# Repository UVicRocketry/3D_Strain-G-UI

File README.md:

# 3D_Strain-G-UI
Welcome to 3D_Strain-G-UI: a 3D PyQT/PyQTGraph GUI for rocket fuselage bending analysis using strain gauges!

Originally designed for Uvic Rocketry's 10k/Xenia-1 rocket, it is a general piece of software capable of supporting any number of strain gauges, and any rocket shape.

## Basic Requirements
* python3 and pip3
* The following libraries installed using pip3
	* PyQT5
	* numpy
	* numpy-stl
	* pyserial
	* pyqtgraph
	* pyopengl
	* qdarkstyle

Additionally, if you would like to use the live mode of this software, an Arduino programmed with `MPU6050_Demp_Sketch.ino` or similar device capable of serial communication should be connected to the computer.

## Setup
First clone the respository
```
git clone https://github.com/UVicRocketry/3D_Strain-G-UI
```
Then open a terminal in the `3D_Strain-G-UI` folder and run
```
python 3D_Backend.py
```
to start the program.

## Interface Overview
Upon first launch, the following interface is shown. This shows graphs of stats such as yaw, pitch, roll, altitude, etc.

_Note: only some of these graphs are implemented right now_

Selecting Tab2 of the UI, the main interface is shown.

Here is where the magic happens. The upper left of the UI contains file management controls, below are playback controls, and bottom left are current rocket environmental variables.

## Selecting a Rocket
3D-Strain-G-UI allows `.rocket` configuration files to be loaded via the `Load Rocket` button. A sample rocket called `10K.rocket` is included for testing.

## Loading a Log File
CSV log files formatted as `time,yaw,pitch,roll,altitude,strain1,strain2....` can be loaded for playback using the `Load Log File` button. A sample log file called `Sample_Flight_Data.csv` is included for testing with `10K.rocket`.

## Basic Usage
Load the `10K.rocket` and `Sample_Flight_Data.csv` files into the program. This should show a model of SpaceX's starship created by Arturo R. 

Next, test the playback by pressing play button. The Starship should display strain data, altitude, etc as it reads the log file.

Click and drag on the rocket to orbit around. Zoom using the scroll wheel, and pan using scroll click. Pause playback using the play button, and reset to the initial view using the `Reset View` button.

Using the slider under the 3D view, scrub through the log file to find apogee. Adjust the framerate slider and begin playback to watch the apogee in slow motion.

Pause playback during a particularly colorful section of the logfile which indicates high strain. In the table beneath the Yaw, Pitch etc. data, select a cell to highlight the strain sensor on the rocket responsible for that data. The section of the model will glow pink when selected.

## Creating a Model
Since the models used by the software are `.STL`, any CAD program can be used to create them. 

Specific naming must be used for the strain sections of the following form: `foo-strain_section-n.STL` where n = 1,2,3,4... It is recommended to use linear and radial patterns to automatically number the parts according to this naming convention, however the parts can be named manually as well. Arturo's Starship Solidworks assembly is included as a reference. Other components of the assembly do not need to follow any particular naming convention. Shown below is the feature tree of the included assembly.

To ensure that the rocket in the 3D view orbits around the center of mass, the assembly must be treated in a certain way. First, mate the CoM of the assembly to the origin of the assembly. Then, when exporting the assembly as an STL, click options, then check the box labled "Do not translate STL output data to positive space".

## Creating a .Rocket Configuration
Configuration files can be created that specify the location of STL files, color sensitivity and other parameters. Below is the `10K.rocket` config included.

```
{
    "NAME": "Arturo's Starship",
    "STL_DIRECTORY" : "STL_Files",
    "RINGS" : 3,
    "SG_PER_RING" : 4,
    "COLOR_SENSITIVITY" : 0.02
}
```

This file can be reused as is with the `STL_DIRECTORY` changed to the relative location of the STLs desired. `RINGS` and `SG_PER_RING` are discussed in the next section.

## Ring Terminology
The software was originally written to consider the strain gauges in "rings" that are placed circumferentially at a given section of the fuselage. Multiple rings are placed at various points of the fuselage to measure strain in those areas. Later however, it was determined that this is not a limitation that need to be applied to the software, and strain gauges do not need to be organized in the fashion. The code could be easily adapted to support say strain gauges in the fins or nosecone. Regardless, the terminology stuck, so until the code is modified, this is how things are.

What this means is in configuration files, the number of rings, and number of strain gauges per ring must be specified. The included sample files contain 12 strain gauges arranged in 3 rings of 4 gauges. The `.rocket` file reflects this.

## Further Work
It would be nice to implement the rest of the graphs in Tab1. Also, removing any ring structure dependence in the code would help to simplify the code and make it more flexible. The `Rocket` class should also be split into a seperate file to make the source files smaller.

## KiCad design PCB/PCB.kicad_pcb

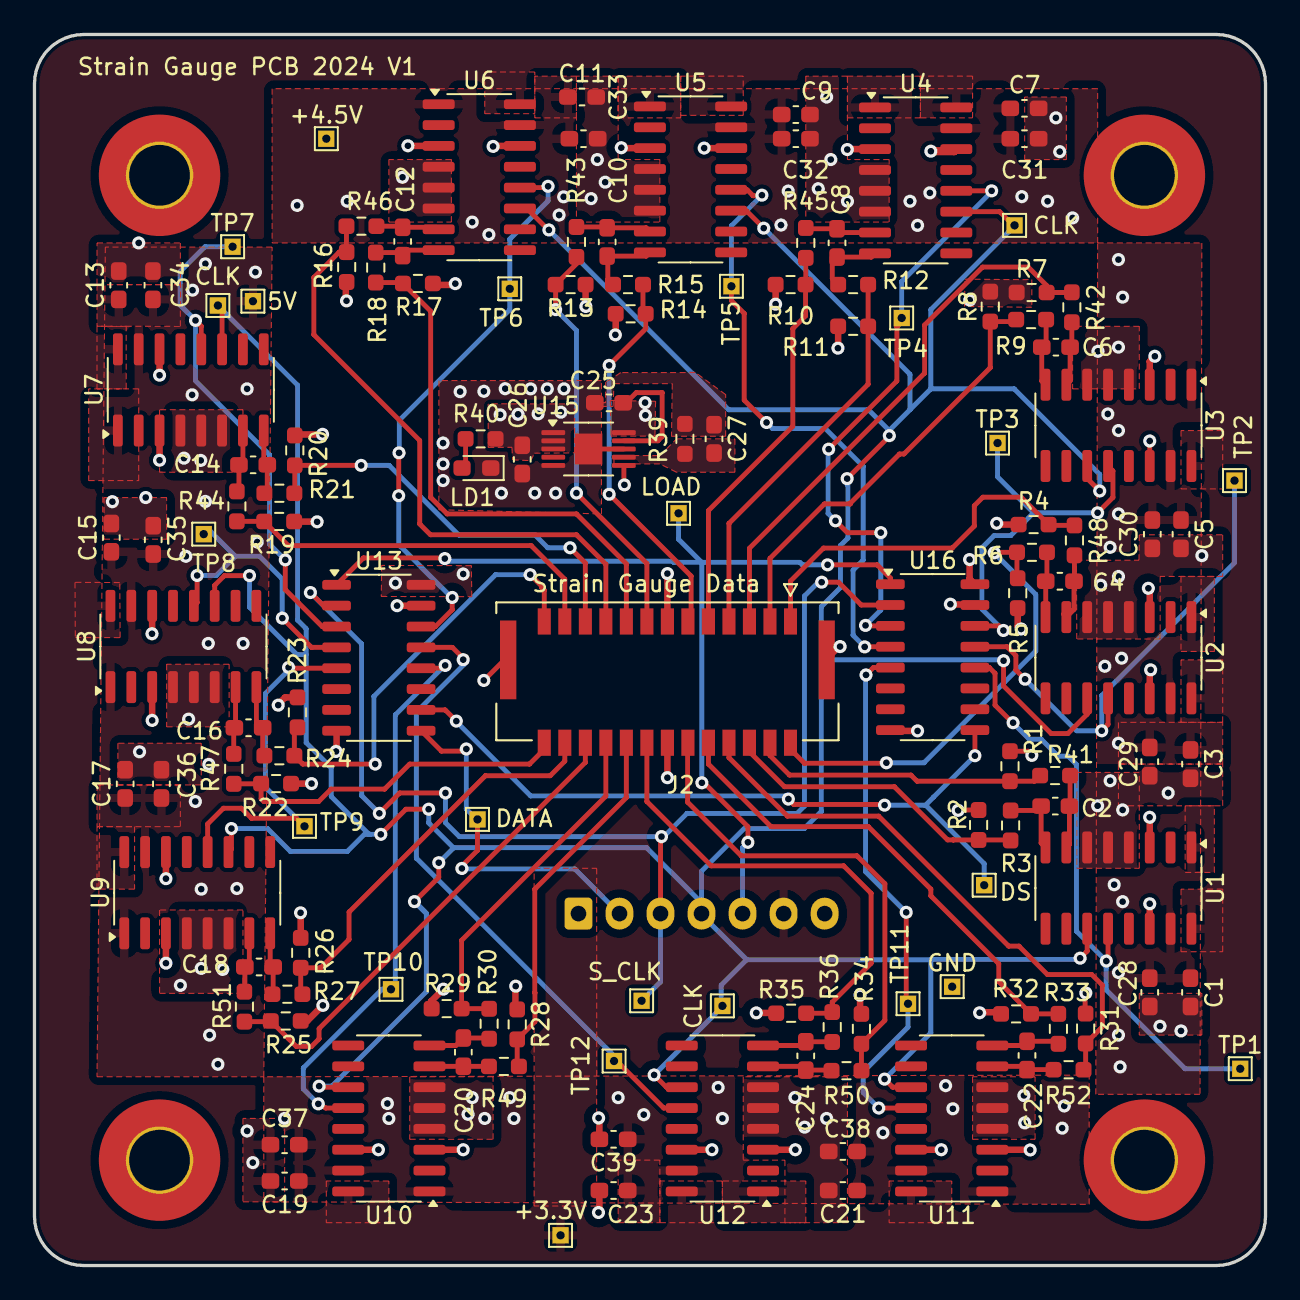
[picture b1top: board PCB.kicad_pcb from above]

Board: 4 copper layers, 75.0 x 75.0 mm, 134 parts (1 on the bottom side), 71 nets.

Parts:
5V: 5V; TestPoint_THTPad_1.0x1.0mm_Drill0.5mm
+3.3V: 3.3V; TestPoint_THTPad_1.0x1.0mm_Drill0.5mm
+4.5V: 4.5V; TestPoint_THTPad_1.0x1.0mm_Drill0.5mm
C1, C3, C5, C7, C9, C11, C13, C15, C17, C19, C21, C23: 10U; C_0603_1608Metric_Pad1.08x0.95mm_HandSolder
C2, C4, C6, C8, C10, C12, C14, C16, C18, C20, C22, C24, C28, C29, C30, C31, C32, C33, C34, C35, C36, C37, C38, C39: U01; C_0603_1608Metric_Pad1.08x0.95mm_HandSolder
C25, C26, C27: 4.7U; C_0603_1608Metric_Pad1.08x0.95mm_HandSolder
CLK: HX_CLK; TestPoint_THTPad_1.0x1.0mm_Drill0.5mm
CLK#2, CLK#3: HX_CLK; TestPoint_THTPad_1.0x1.0mm_Drill0.5mm
DATA: DATA; TestPoint_THTPad_1.0x1.0mm_Drill0.5mm
DS: DS; TestPoint_THTPad_1.0x1.0mm_Drill0.5mm
GND: GND; TestPoint_THTPad_1.0x1.0mm_Drill0.5mm
H1, H2, H3, H4: MountingHole; MountingHole_3.7mm_Pad_TopBottom
J1: Conn_01x06_Female; JST_XH_B7B-XH-A_1x07_P2.50mm_Vertical
J2: 5054332681; MOLEX_5054332681
LD1: LED; LED_0603_1608Metric_Pad1.05x0.95mm_HandSolder
LOAD: LOAD; TestPoint_THTPad_1.0x1.0mm_Drill0.5mm
R1, R2, R4, R5, R7, R8, R10, R11, R13, R14, R16, R17, R19, R20, R22, R23, R25, R26, R28, R29, R31, R32, R34, R35: 350; R_0603_1608Metric_Pad0.98x0.95mm_HandSolder
R3, R6, R9, R12, R15, R18, R21, R24, R27, R30, R33, R36, R41, R42, R43, R44, R45, R46, R47, R48, R49, R50, R51, R52: 100; R_0603_1608Metric_Pad0.98x0.95mm_HandSolder
R39: 45K; R_0603_1608Metric_Pad0.98x0.95mm_HandSolder
R40: 1k; R_0603_1608Metric_Pad0.98x0.95mm_HandSolder
S_CLK: S_CLK; TestPoint_THTPad_1.0x1.0mm_Drill0.5mm
TP1: SG1; TestPoint_THTPad_1.0x1.0mm_Drill0.5mm
TP2: SG2; TestPoint_THTPad_1.0x1.0mm_Drill0.5mm
TP3: SGD3; TestPoint_THTPad_1.0x1.0mm_Drill0.5mm
TP4: SG4; TestPoint_THTPad_1.0x1.0mm_Drill0.5mm
TP5: SG5; TestPoint_THTPad_1.0x1.0mm_Drill0.5mm
TP6: SG6; TestPoint_THTPad_1.0x1.0mm_Drill0.5mm
TP7: SG7; TestPoint_THTPad_1.0x1.0mm_Drill0.5mm
TP8: SG8; TestPoint_THTPad_1.0x1.0mm_Drill0.5mm
TP9: SG9; TestPoint_THTPad_1.0x1.0mm_Drill0.5mm
TP10: SG10; TestPoint_THTPad_1.0x1.0mm_Drill0.5mm
TP11: SG11; TestPoint_THTPad_1.0x1.0mm_Drill0.5mm
TP12: SG12; TestPoint_THTPad_1.0x1.0mm_Drill0.5mm
U1, U2, U3, U4, U5, U6, U7, U8, U9, U10, U11, U12: Hx711; SOIC-16_3.9x9.9mm_P1.27mm
U13, U16: 74HC165; SO-16_3.9x9.9mm_P1.27mm
U15: LT3042xMSE; MSOP-10-1EP_3x3mm_P0.5mm_EP1.68x1.88mm

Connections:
4.5V: +4.5V.1, C25.1, J2.13, J2.14, U1.3 (AVDD), U2.3 (AVDD), U3.3 (AVDD), U4.3 (AVDD), U5.3 (AVDD), U6.3 (AVDD), U7.3 (AVDD), U8.3 (AVDD), U9.3 (AVDD), U10.3 (AVDD), U11.3 (AVDD), U12.3 (AVDD), U15.9 (OUTS), U15.10 (OUT)
+3.3V: +3.3V.1, J1.6, U1.16 (DVDD), U2.16 (DVDD), U3.16 (DVDD), U4.16 (DVDD), U5.16 (DVDD), U6.16 (DVDD), U7.16 (DVDD), U8.16 (DVDD), U9.16 (DVDD), U10.16 (DVDD), U11.16 (DVDD), U12.16 (DVDD)
+5V: 5V.1, C1.1, C3.1, C5.1, C7.1, C9.1, C11.1, C13.1, C15.1, C17.1, C19.1, C21.1, C23.1, C26.2, C28.1, C29.1, C30.1, C31.1, C32.1, C33.1, C34.1, C35.1, C36.1, C37.1, C38.1, C39.1, J1.7, R40.1, U1.1 (VSUP), U1.15 (RATE), U2.1 (VSUP), U2.15 (RATE), U3.1 (VSUP), U3.15 (RATE), U4.1 (VSUP), U4.15 (RATE), U5.1 (VSUP), U5.15 (RATE), U6.1 (VSUP), U6.15 (RATE), U7.1 (VSUP), U7.15 (RATE), U8.1 (VSUP), U8.15 (RATE), U9.1 (VSUP), U9.15 (RATE), U10.1 (VSUP), U10.15 (RATE), U11.1 (VSUP), U11.15 (RATE), U12.1 (VSUP), U12.15 (RATE), U13.16 (VCC), U15.1 (IN), U15.2 (IN), U15.3 (EN/UV), U15.6 (PGFB), U16.16 (VCC)
/DATA: DATA.1, J1.2, U13.9 (Q7)
/DOUT: TP1.1, U1.12 (DOUT), U16.12 (D1)
/DOUT1: TP3.1, U3.12 (DOUT), U16.14 (D3)
/DOUT2: TP5.1, U5.12 (DOUT), U16.4 (D5)
/DOUT3: TP7.1, U7.12 (DOUT), U13.3 (D4)
/DOUT4: TP9.1, U9.12 (DOUT), U13.5 (D6)
/DOUT5: TP11.1, U11.12 (DOUT), U16.5 (D6)
/DOUT9: TP4.1, U4.12 (DOUT), U16.3 (D4)
/DOUT10: TP6.1, U6.12 (DOUT), U13.14 (D3)
/DOUT11: TP8.1, U8.12 (DOUT), U13.4 (D5)
/DOUT12: TP2.1, U2.12 (DOUT), U16.13 (D2)
/DOUT13: TP10.1, U10.12 (DOUT), U13.12 (D1)
/DOUT14: TP12.1, U12.12 (DOUT), U13.13 (D2)
/H1N: J2.3, R8.2, R9.2
/H1P: J2.5, R7.2, R42.2
/H2N: J2.11, R14.2, R15.2
/H2P: J2.15, R13.2, R43.2
/H3N: J2.21, R20.2, R21.2
/H3P: J2.23, R19.2, R44.2
/H4N: J2.24, R26.2, R27.2
/H4P: J2.22, R25.2, R51.2
/H5N: J2.10, R32.2, R33.2
/H5P: J2.8, R31.2, R52.2
/H9N: J2.7, R11.2, R12.2
/H9P: J2.9, R10.2, R45.2
/H10N: J2.17, R17.2, R18.2
/H10P: J2.19, R16.2, R46.2
/H11N: J2.25, R23.2, R24.2
/H11P: J2.26, R22.2, R47.2
/H12N: J2.2, R5.2, R6.2
/H12P: J2.1, R4.2, R48.2
/H13N: J2.20, R29.2, R30.2
/H13P: J2.18, R28.2, R49.2
/H14N: J2.16, R35.2, R36.2
/H14P: J2.12, R34.2, R50.2
/HN: J2.6, R2.2, R3.2
/HP: J2.4, R1.2, R41.2
/LOAD: J1.5, LOAD.1, U13.1 (~PL), U16.1 (~PL)
/SET: C27.2, R39.2, U15.7 (SET)
/S_CLK: J1.3, S_CLK.1, U13.2 (CP), U16.2 (CP)
GND: C1.2, C3.2, C5.2, C7.2, C9.2, C11.2, C13.2, C15.2, C17.2, C19.2, C21.2, C23.2, C25.2, C26.1, C27.1, C28.2, C29.2, C30.2, C31.2, C32.2, C33.2, C34.2, C35.2, C36.2, C37.2, C38.2, C39.2, GND.1, J1.1, J2.S1 (SHIELD1), J2.S2 (SHIELD2), LD1.1 (K), R1.1, R2.1, R4.1, R5.1, R7.1, R8.1, R10.1, R11.1, R13.1, R14.1, R16.1, R17.1, R19.1, R20.1, R22.1, R23.1, R25.1, R26.1, R28.1, R29.1, R31.1, R32.1, R34.1, R35.1, R39.1, U1.4 (VFB), U1.5 (AGND), U1.6 (VBG), U1.14 (X1), U2.4 (VFB), U2.5 (AGND), U2.6 (VBG), U2.14 (X1), U3.4 (VFB), U3.5 (AGND), U3.6 (VBG), U3.14 (X1), U4.4 (VFB), U4.5 (AGND), U4.6 (VBG), U4.14 (X1), U5.4 (VFB), U5.5 (AGND), U5.6 (VBG), U5.14 (X1), U6.4 (VFB), U6.5 (AGND), U6.6 (VBG), U6.14 (X1), U7.4 (VFB), U7.5 (AGND), U7.6 (VBG), U7.14 (X1), U8.4 (VFB), U8.5 (AGND), U8.6 (VBG), U8.14 (X1), U9.4 (VFB), U9.5 (AGND), U9.6 (VBG), U9.14 (X1), U10.4 (VFB), U10.5 (AGND), U10.6 (VBG), U10.14 (X1), U11.4 (VFB), U11.5 (AGND), U11.6 (VBG), U11.14 (X1), U12.4 (VFB), U12.5 (AGND), U12.6 (VBG), U12.14 (X1), U13.8 (GND), U13.15 (~CE), U15.5 (ILIM), U15.8 (GND), U15.11 (GND), U16.8 (GND), U16.15 (~CE)
HX_CLK: CLK.1, CLK#2.1, CLK#3.1, J1.4, U1.11 (PD_SCK), U2.11 (PD_SCK), U3.11 (PD_SCK), U4.11 (PD_SCK), U5.11 (PD_SCK), U6.11 (PD_SCK), U7.11 (PD_SCK), U8.11 (PD_SCK), U9.11 (PD_SCK), U10.11 (PD_SCK), U11.11 (PD_SCK), U12.11 (PD_SCK)
unnamed: LD1.2 (A), R40.2
unnamed: C2.2, R3.1, U1.8 (INA+)
unnamed: C2.1, R41.1, U1.7 (INA-)
unnamed: C4.2, R6.1, U2.8 (INA+)
unnamed: C4.1, R48.1, U2.7 (INA-)
unnamed: C6.2, R9.1, U3.8 (INA+)
unnamed: C6.1, R42.1, U3.7 (INA-)
unnamed: C8.2, R12.1, U4.8 (INA+)
unnamed: C8.1, R45.1, U4.7 (INA-)
unnamed: C10.2, R15.1, U5.8 (INA+)
unnamed: C10.1, R43.1, U5.7 (INA-)
unnamed: C12.2, R18.1, U6.8 (INA+)
unnamed: C12.1, R46.1, U6.7 (INA-)
unnamed: C14.2, R21.1, U7.8 (INA+)
unnamed: C14.1, R44.1, U7.7 (INA-)
unnamed: C16.2, R24.1, U8.8 (INA+)
unnamed: C16.1, R47.1, U8.7 (INA-)
unnamed: C18.2, R27.1, U9.8 (INA+)
unnamed: C18.1, R51.1, U9.7 (INA-)
unnamed: C20.2, R30.1, U10.8 (INA+)
unnamed: C20.1, R49.1, U10.7 (INA-)
unnamed: C22.2, R33.1, U11.8 (INA+)
unnamed: C22.1, R52.1, U11.7 (INA-)
unnamed: C24.2, R36.1, U12.8 (INA+)
unnamed: C24.1, R50.1, U12.7 (INA-)
unnamed: DS.1, U13.10 (DS), U16.9 (Q7)

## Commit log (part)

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2020-12-18 Adds local code/CAD
2020-12-24 Fixes spelling
2020-12-24 Changes file names. Removes extra .py file
2020-12-30 Removes extra CAD
2020-12-30 Finshes Rocket class
2020-12-30 Removes altitude grids, renames timer method
2021-01-01 Removes redundant CAD assembly
2021-01-01 Begins framework for strain section coloring
2021-01-02 Adds framework for GUI buttons
2021-01-06 Adds layouts and panels
2021-01-07 Adds file dialog box
2021-01-10 Adds mesh coloring based on strain reading
2021-01-11 Adds more support for strain coloring
2021-01-13 Arduino data now colors strain sections
2021-01-14 More color support and debugging
2021-01-21 Adds log file button
2021-01-21 Adds backend to log file button
2021-01-21 clear button implementation
2021-01-21 ui file update
2021-01-21 Fixes name of button
2021-01-21 Renames log file line edit to match function
2021-01-22 Adds comments
2021-01-22 Lays foundation for log file reading
2021-01-24 Basic logfile reading implemented
2021-01-24 Updates cg of cad.
2021-01-25 Strain section coloring functional now
2021-01-25 Adds framerate slider, and altitude grid
2021-01-25 New test data, + bug fixes
2021-01-25 Adds better data file.
2021-01-25 Fixes framerate slider. Adds altitude callout
2021-01-28 GUI btn update
2021-01-28 gui update
2021-01-28 gui update 2
2021-01-31 Fixes altitude grids. Breaks Rotation.
2021-01-31 Fixes rotation + minor tweaks
2021-01-31 Adds pause/play and frame stepping
2021-01-31 Fully implements play/pause/step btns
2021-01-31 Camera now zooms out initially
2021-02-02 Adds "Reset View" btn to gui.
2021-02-04 colorsensitivity slider added
2021-02-04 color sensitivity update
2021-02-04 Lowers color sensitivity
2021-02-13 Adds new icons to gui
2021-02-16 Adds more icons
2021-02-18 Relative file paths for icons
2021-02-18 Fixes last icon file path
2021-02-22 scrub slider update
2021-02-23 New starship model cad and stl files
2021-02-23 Adds scrub slider
2021-02-24 Scrub slider now moves during playback
2021-02-25 Adds table for strain values
2021-02-25 Adds table
2021-02-25 strain display
2021-02-25 Finishes strain table implementation
2021-02-27 Fixes cs slider
2021-02-28 pry table update
2021-02-28 ypr casted to string to fix table output
2021-02-28 pry done
2021-02-28 pry update
2021-03-11 File browser filters by .csv + minor tweaks
2021-03-11 Adds .rocket support
2021-03-11 Adds dark theme and uvr logo
2021-03-18 Adds green to color gradient
2021-03-25 Adds better support for green strain coloring
2021-03-25 Adds comment
2021-03-25 strain table update
2021-03-25 compression spectrum legend
2021-03-28 Adds strain selection highlighting
2021-03-28 Adds KiCad PCB project folder
2021-03-28 Fixes folder name
2021-03-28 Adds gui update helper method
2021-03-29 Minor pcb modifications
2021-04-01 More radial layout
2021-04-01 changed UVIC ROCKETRY icon in bottom left
2021-04-01 Removes old UVR, adds tab to .UI
2021-04-01 Re-adds UVR logo
2021-04-01 Bug fixes
2021-04-01 adds draft 1 layout for second tab
2021-04-04 Generated requirements.txt
2021-04-04 Edit Readme and Create Dependency Installer
2021-04-04 Add Run.bat
    Super complex file I spent all day working on.
2021-04-04 Fixed run.bat And Silenced runSetup.bat
2021-04-04 Renaming and update README
2021-04-04 Fix emoji
2021-04-08 Adds some basic backend for 2nd tab
2021-04-11 Removes PCB (Moved to GrabCAD)
2021-04-15 Chagnes name of flight data
2021-04-15 Changes rocket class vars to lists
2021-04-15 Fixes merge issues
2021-04-15 Adds backend to ypr graph
2021-05-20 Updates items to follow naming convention
2021-05-20 graphs update
2021-05-24 Adds ypr graph lines
2021-06-04 Fixes some issues with livemode
2021-06-05 Upgraded Arduino sketch.
2021-06-09 Adds SG support to sketch
2022-04-02 Update README, remove license.
2022-04-02 Fix images in README
2022-05-30 Add PCB
2022-05-30 Reroute PCB traces
2022-05-30 Final Gerbers
2022-07-18 Set RATE high for 80hz
2022-07-18 Sample data for testing
2022-09-21 Add hierachial and shift registers
2022-09-24 Swap shift registers. Start board layout
2022-09-24 Start radial layout
2022-09-24 Cont. radial layout
2022-09-24 Finish radial layout
2022-10-15 Add second decoupling cap to HXs
2022-10-15 Remove old gerbers
2022-10-17 Finish trace routing
2022-10-21 Increase post clearance. Optimize traces
2022-11-02 Final revisions before printing
2022-11-02 Create gerbers
2023-04-25 Fix _CE so it is now LOW
2023-04-25 Fix _CE on PCB. Add rectangular radial pads.
2023-07-26 Switch VDD to 3.3V. Ready for comp
2024-01-24 Current version
    Pulled everything into github
2024-01-29 Schematic update
    Updated ports to ground
2024-02-03 Updates to layout
    Started using radial, sides are going everywhere.
2024-02-05 Updated pcb
    Working on setting the positions to be adequate before tracing
2024-02-08 Connector update
    Changed the connector I found to a db25 and adjusted the radius of components to compensate
2024-02-16 Created outline and updated pcb
    Started work on tracing the pcb now that I have a complete layout with a wiring channel cut out. Two planes have been laid out
2024-02-17 Updated pcb with tracing
    2 more planes have been added and many wires are going around including clock lines
2024-02-17 Updated layout
    Due to some complications during the first attempt at tracing, a new version of the board had to be created
2024-02-22 PCB routing
    Started work on two ground planes and wiring each section to each other.
2024-02-22 Updated pcb
    Added an extra ground plane and am working on adding the necessary sections and points to the planes.
2024-02-23 updated PCB
    Current version with errors
2024-02-24 Initial routing completed
    All locations have been routed, will do a drc to check
2024-02-24 Board complete
    This version passes the design rules checker. The only thing left is to get a good outline and then we are set for pcb review.
2024-02-24 Current final version
    Cleaned up unconnected items
2024-02-27 PCB Finalized
    Finalized PCB and will be looking at purchase options.
    Edge cuts fixed
2024-03-01 Newest version kicad 8
    Did some basic work on the 3d model.
    Use this for pcb review
2024-03-01 New step
    PCB
2024-03-01 git ignore
2024-03-03 Final Radial version
    Solved a lot of problems, but restarting.
2024-03-05 Beginning new layout
    As I am placing components on the board, I am getting the impression that 70 mm by 70 mm is too small of a board for what I am attempting. The through hole connectors that I am looking at are too big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
2024-03-05 Imported other downloaded connector
    Imported other downloaded through hole connector to compare sizes with another one, even though they will be on different sides from the top of the board. I'm just concerned that I won't be able to w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
2024-03-06 Changed size of pcb
    PCB size increased by 725 square mm by increasing size to a 75 mm by 75 mm square. Dout and the clock for the hx711s have been wired as well as the control wires for the shift registers.
2024-03-06 Don't commit backups
2024-03-07 New 75 by 75 mm
    Dout has been traced, mostly on the same plane and have started on some of the required parts for the individual hx711 and will continue setting up sequential zones to reduce wires.
2024-03-07 Board complete save silkscreen
    Every single wire has been traced and there are no errors with a design rules checker.
2024-03-07 Spotted a possible error and fixed it
    The 3v3 zone had a via in it that reduced the size of the zone to a thickness that was too thin and would have likely led to eventual errors running 3v3 from the supply from the connector.
2024-03-07 Changed planes
    Changed the no net plane to a ground plane and connected everything.
2024-03-08 Updated some traces to get better flow.
    Updated traces on the front plane to reduce bends.
2024-03-08 New update
    For review
2024-03-09 Updated traces and new board settings
    All silkscreens have also been moved and passes drc. All voltage traces not on pours or that are only connected on one to pours have been updated. Last thing to do is add the martlet, my name among a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
2024-03-12 Fixed power lines on the board
    Power lines are all now .4 mm unless they are at the linear regulator, in which case they are .25 mm
2024-03-12 Minor changes to ensure wires are running straigther
    Wires adjusted to allow for more direct pathing
2024-03-13 Fixed pour issues
    Around the linear regulator, the pour was changed to be a solid fill for the 4.5 Volt zone and the 5V and included the addition of a dozen vias to connect the layers.
2024-03-14 PCB improvements made after conversing with Aila
    Inner 5V boundary pour on the front layer has been replaced by four separate rectangle pours and the inner ground pour on the front plane has been replaced with individual separate ground pours for p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
2024-03-14 Screenshots added
    two screen snips for front and back views of the pcb are added.
2024-03-14 Updated 7 pin header pinout
    Pinout has been adjusted to match the pinout of the flight computer.
2024-03-15 Rotated connector to better fit flight computer
    Addition of a 3v3 zone expansion and passes drc.
2024-03-18 Board updated for linear regulator and fills
    Fills around each of the hx711 capacitor assemblies were changed to solid fills and the layout around the linear regulator was optimized to better fit with the data sheet.
2024-03-19 Added test points and changed labels
    Added test points for nearly every single cable. Labels on individual sections changed to better reflect the actual board.
2024-03-19 Silkscreen updated
    The strain gauges are correctly labeled now as well as the test points for all individual hx711 amplifiers. All the voltages are completely labeled as well. There are many 4.5V, 5V and 3.3V test poin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
2024-03-21 Updated Linear Regulator Layout
    Linear regulator layout has been updated to better match the data sheet and the labels for every test point have been cleaned up.
2024-03-23 Fixed linear regulator
    Linear regulator has been set up to Mateo's proportions. Test points have also been moved.
2024-03-26 Fixed silkscreen
    Silkscreen updated to better suit everything as a label was not corrected earlier.
2024-03-29 Post review first draft
    Taking into account many of the pieces of feedback received in the pcb review on Wednesday by changing the locations of the shift registers and rewiring accordingly.
2024-03-31 PCB Review feedback implemented
    All traces applied, test points moved, voltages are available. Test points have been clustered together on the schematic. Silkscreen passes DRC as to wire tolerances.
2024-03-31 Silkscreen updated
    Data1 changed to Data
2024-03-31 Addressed via feedback
    Due to the feedback about vias, they were changed to follow recommendations.
2024-03-31 PCB layout changed
    Consolidated the layout for a problematic area to allow for a larger 3v3 zone around its port.
2024-03-31 Wire changed
    A trace was relocated a little bit to allow for more current flow on the 3v3 zone
2024-04-01 PCB Wheatstone Bridge updates
    Several of the wheatstone bridge sections have been changed to fit the more compact style used elsewhere on the board to reduce the need for vias on analog traces.
2024-04-01 Updated PCB
    An extra test point was recognized and removed.
2024-04-01 Silkscreen changed
    One silkscreen label shifted a bit to ensure better readability and a capacitor shifted to a better position.
2024-04-01 PCB updated
    Straightened the interfacing between vias and compacted the layout for a couple of the wheatstone bridge layouts.
2024-04-01 Traces changed
    Tracing has changed as there were unconnected vias on some of the output traces.
2024-04-05 Traces cleaned up for review
    power traces have been changed to .4 mm for all sides.
    Minor trace adjustments were added.
2024-04-13 Updated gerbers and ready to order
    Still need to figure out how to add components to the bill of materials with the digikey part numbers, probably can do that in the descriptions.
2024-04-14 Change in updates
